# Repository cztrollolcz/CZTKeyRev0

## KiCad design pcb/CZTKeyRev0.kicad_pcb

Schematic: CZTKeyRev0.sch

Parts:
BJ_LED5V1: Barrel_Jack_Switch; BarrelJackP1
D0, D1, D2, D3, D4, D5, D6, D7, D8, D9, D10, D11, D12, D13, D14, D15, D16, D17, D18, D19, D20, D21, D22, D23, D24, D25, D26, D27, D28, D29, D30, D31, D32, D33, D34, D35, D36, D37, D38, D39, D40, D41, D42, D43, D44, D45, D46, D47, D48, D49, D50, D51, D52, D53, D54, D55, D56, D57, D58, D59, D60, D61, D62, D63, D64, D65, D66, D67, D68, D69, D70, D71, D72, D73, D74, D75, D76, D77, D78, D79, D80, D81, D82, D83, D84, D85, D86: D_Small; D_DO-35_SOD27_P5.08mm_Vertical_KathodeUp
DC1, DC2, DC3, DC4, DC5, DC6, DC7, DC8, DC9, DC10, DC11, DC12, DC13, DC14, DC15, DC16, DC17, DC18, DC19, DC20, DC21, DC22, DC23, DC24, DC25, DC26, DC27, DC28, DC29, DC30, DC31, DC32, DC33, DC34, DC35, DC36, DC37, DC38, DC39, DC40, DC41, DC42, DC43, DC44, DC45, DC46, DC47, DC48, DC49, DC50, DC51, DC52, DC53, DC54, DC55, DC56, DC57, DC58, DC59, DC60, DC61, DC62, DC63, DC64, DC65, DC66, DC67, DC68, DC69, DC70, DC71, DC72, DC73, DC74, DC75, DC76, DC78, DC79, DC80, DC81, DC82, DC83, DC84, DC85, DC86, DC87: 100n; C_0805_2012Metric_Pad1.15x1.40mm_HandSolder
ENC1: Rotary_Encoder_Switch; RotaryEncoder_Alps_EC11E-Switch_Vertical_H20mm
EXT_IC1: 74LVC1G17GV,125; SOT95P275X110-5N; Mouser Part Number 771-LVC1G17GV125
LED1, LED2, LED3, LED4, LED5, LED6, LED7, LED8, LED9, LED10, LED11, LED12, LED13, LED14, LED15, LED16, LED17, LED18, LED19, LED20, LED21, LED22, LED23, LED24, LED25, LED26, LED27, LED28, LED29, LED30, LED31, LED32, LED33, LED34, LED35, LED36, LED37, LED38, LED39, LED40, LED41, LED42, LED43, LED44, LED45, LED46, LED47, LED48, LED49, LED50, LED51, LED52, LED53, LED54, LED55, LED56, LED57, LED58, LED59, LED60, LED61, LED62, LED63, LED64, LED65, LED66, LED67, LED68, LED69, LED70, LED71, LED72, LED73, LED74, LED75, LED76, LED78, LED79, LED80, LED81, LED82, LED83, LED84, LED85, LED86, LED87: YS-SK6812MINI-E; SK6812MINIE-simple
MX_0, MX_1, MX_2, MX_3, MX_4, MX_5, MX_6, MX_7, MX_8, MX_9: MX-NoLED; MX-1U-NoLED
MX_A1: MX-NoLED; MX-1U-NoLED
MX_ALT_L1: MX-NoLED; MX-1.25U-NoLED
MX_ALT_R1: MX-NoLED; MX-1.5U-NoLED
MX_B1: MX-NoLED; MX-1U-NoLED
MX_BACKSPACE1: MX-NoLED; MX-2U-NoLED
MX_BCKSLASH1: MX-NoLED; MX-1.5U-NoLED
MX_BR_L1: MX-NoLED; MX-1U-NoLED
MX_BR_R1: MX-NoLED; MX-1U-NoLED
MX_C1: MX-NoLED; MX-1U-NoLED
MX_CAPS1: MX-NoLED; MX-1.75U-NoLED
MX_COMMA1: MX-NoLED; MX-1U-NoLED
MX_CTRL_L1: MX-NoLED; MX-1.25U-NoLED
MX_CTRL_R1: MX-NoLED; MX-1.5U-NoLED
MX_D1: MX-NoLED; MX-1U-NoLED
MX_DELETE1: MX-NoLED; MX-1U-NoLED
MX_DOT1: MX-NoLED; MX-1U-NoLED
MX_DOWN1: MX-NoLED; MX-1U-NoLED
MX_E1: MX-NoLED; MX-1U-NoLED
MX_ENTER1: MX-NoLED; MX-2.25U-NoLED
MX_EQUAL1: MX-NoLED; MX-1U-NoLED
MX_ESC1: MX-NoLED; MX-1U-NoLED
MX_F0, MX_F1, MX_F2, MX_F3, MX_F4, MX_F5, MX_F6, MX_F7, MX_F8, MX_F9, MX_F10, MX_F11, MX_F12: MX-NoLED; MX-1U-NoLED
MX_G1: MX-NoLED; MX-1U-NoLED
MX_H1: MX-NoLED; MX-1U-NoLED
MX_I1: MX-NoLED; MX-1U-NoLED
MX_INSERT1: MX-NoLED; MX-1U-NoLED
MX_J1: MX-NoLED; MX-1U-NoLED
MX_K1: MX-NoLED; MX-1U-NoLED
MX_L1: MX-NoLED; MX-1U-NoLED
MX_LEFT1: MX-NoLED; MX-1U-NoLED
MX_M1: MX-NoLED; MX-1U-NoLED
MX_MAC1, MX_MAC2, MX_MAC3, MX_MAC4, MX_MAC5: MX-NoLED; MX-1U-NoLED
MX_MINUS1: MX-NoLED; MX-1U-NoLED
MX_N1: MX-NoLED; MX-1U-NoLED
MX_O1: MX-NoLED; MX-1U-NoLED
MX_P1: MX-NoLED; MX-1U-NoLED
MX_PGDWN1: MX-NoLED; MX-1U-NoLED
MX_PGUP1: MX-NoLED; MX-1U-NoLED
MX_PRTSC1: MX-NoLED; MX-1U-NoLED
MX_Q1: MX-NoLED; MX-1U-NoLED
MX_QUOTE1: MX-NoLED; MX-1U-NoLED
MX_R1: MX-NoLED; MX-1U-NoLED
MX_RIGHT1: MX-NoLED; MX-1U-NoLED
MX_S1: MX-NoLED; MX-1U-NoLED
MX_SEMIC1: MX-NoLED; MX-1U-NoLED
MX_SHIFT_L1: MX-NoLED; MX-2.25U-NoLED
MX_SHIFT_R1: MX-NoLED; MX-1.75U-NoLED
MX_SLASH1: MX-NoLED; MX-1U-NoLED
MX_SPACE1: MX-NoLED; MX-6.25U-NoLED
MX_T1: MX-NoLED; MX-1U-NoLED
MX_TAB1: MX-NoLED; MX-1.5U-NoLED
MX_TILDE1: MX-NoLED; MX-1U-NoLED
MX_U1: MX-NoLED; MX-1U-NoLED
MX_UP1: MX-NoLED; MX-1U-NoLED
MX_V1: MX-NoLED; MX-1U-NoLED
MX_W1: MX-NoLED; MX-1U-NoLED
MX_WIN1: MX-NoLED; MX-1.25U-NoLED
MX_X1: MX-NoLED; MX-1U-NoLED
MX_Y1: MX-NoLED; MX-1U-NoLED
MX_Z1: MX-NoLED; MX-1U-NoLED
OLED1: SSD1306; 128x64OLED
PCB_BC1: MountingHole_Pad; MountingHole_2.2mm_M2_Pad
PCB_BL1: MountingHole_Pad; MountingHole_2.2mm_M2_Pad
PCB_BR1: MountingHole_Pad; MountingHole_2.2mm_M2_Pad
PCB_MC1: MountingHole_Pad; MountingHole_2.2mm_M2_Pad
PCB_TC1: MountingHole_Pad; MountingHole_2.2mm_M2_Pad
PCB_TL1: MountingHole_Pad; MountingHole_2.2mm_M2_Pad
PCB_TR1: MountingHole_Pad; MountingHole_2.2mm_M2_Pad
PLATE_BC1: MountingHole_Pad; MountingHole_2.2mm_M2_Pad
PLATE_BL1: MountingHole_Pad; MountingHole_2.2mm_M2_Pad
PLATE_BR1: MountingHole_Pad; MountingHole_2.2mm_M2_Pad
PLATE_TC1: MountingHole_Pad; MountingHole_2.2mm_M2_Pad
PLATE_TL1: MountingHole_Pad; MountingHole_2.2mm_M2_Pad
PLATE_TR1: MountingHole_Pad; MountingHole_2.2mm_M2_Pad
R1: 300-500 - C422828; R_0805_2012Metric_Pad1.15x1.40mm_HandSolder
U1: proton_c

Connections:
+5V: OLED1.2 (VCC), U1.5V (VBUS(5V_RAW))
COL0: ENC1.S1, MX_MAC1.1 (COL), MX_MAC2.1 (COL), MX_MAC3.1 (COL), MX_MAC4.1 (COL), MX_MAC5.1 (COL), U1.A2
COL1: MX_CAPS1.1 (COL), MX_CTRL_L1.1 (COL), MX_ESC1.1 (COL), MX_SHIFT_L1.1 (COL), MX_TAB1.1 (COL), MX_TILDE1.1 (COL), U1.A1
COL2: MX_1.1 (COL), MX_A1.1 (COL), MX_F1.1 (COL), MX_Q1.1 (COL), MX_WIN1.1 (COL), MX_Z1.1 (COL), U1.A0
COL3: MX_2.1 (COL), MX_ALT_L1.1 (COL), MX_F2.1 (COL), MX_S1.1 (COL), MX_W1.1 (COL), MX_X1.1 (COL), U1.B8
COL4: MX_3.1 (COL), MX_C1.1 (COL), MX_D1.1 (COL), MX_E1.1 (COL), MX_F3.1 (COL), U1.B13 (PB13/SCLK)
COL5: MX_4.1 (COL), MX_F0.1 (COL), MX_F4.1 (COL), MX_R1.1 (COL), MX_V1.1 (COL), U1.B14 (PB14/MISO)
COL6: MX_5.1 (COL), MX_B1.1 (COL), MX_F5.1 (COL), MX_G1.1 (COL), MX_SPACE1.1 (COL), MX_T1.1 (COL), U1.B15 (PB15/MOSI)
COL7: MX_6.1 (COL), MX_F6.1 (COL), MX_H1.1 (COL), MX_N1.1 (COL), MX_Y1.1 (COL), U1.B9
COL8: MX_7.1 (COL), MX_F7.1 (COL), MX_J1.1 (COL), MX_M1.1 (COL), MX_U1.1 (COL), U1.A4 (PA4/SPEAKER1)
COL9: MX_8.1 (COL), MX_COMMA1.1 (COL), MX_F8.1 (COL), MX_I1.1 (COL), MX_K1.1 (COL), U1.A5 (PA5/SPEAKER2)
COL10: MX_9.1 (COL), MX_ALT_R1.1 (COL), MX_DOT1.1 (COL), MX_F9.1 (COL), MX_L1.1 (COL), MX_O1.1 (COL), U1.A6
COL11: MX_0.1 (COL), MX_CTRL_R1.1 (COL), MX_F10.1 (COL), MX_P1.1 (COL), MX_SEMIC1.1 (COL), MX_SLASH1.1 (COL), U1.A7
COL12: MX_BR_R1.1 (COL), MX_F11.1 (COL), MX_LEFT1.1 (COL), MX_MINUS1.1 (COL), MX_QUOTE1.1 (COL), MX_SHIFT_R1.1 (COL), U1.A8
COL13: MX_BR_L1.1 (COL), MX_DOWN1.1 (COL), MX_ENTER1.1 (COL), MX_EQUAL1.1 (COL), MX_F12.1 (COL), U1.A15
COL14: MX_BACKSPACE1.1 (COL), MX_BCKSLASH1.1 (COL), MX_PRTSC1.1 (COL), MX_UP1.1 (COL), U1.A14 (PA14/SWCLK)
COL15: MX_DELETE1.1 (COL), MX_INSERT1.1 (COL), MX_PGDWN1.1 (COL), MX_PGUP1.1 (COL), MX_RIGHT1.1 (COL), U1.A13 (PA13/SWDIO)
ENC_A: ENC1.A, U1.B11
ENC_B: ENC1.B, U1.B12
ENC_S2: D0.2 (A), ENC1.S2
EXT_5V: BJ_LED5V1.1, DC1.2, DC2.2, DC3.2, DC4.2, DC5.2, DC6.2, DC7.2, DC8.2, DC9.2, DC10.2, DC11.2, DC12.2, DC13.2, DC14.2, DC15.2, DC16.2, DC17.2, DC18.2, DC19.2, DC20.2, DC21.2, DC22.2, DC23.2, DC24.2, DC25.2, DC26.2, DC27.2, DC28.2, DC29.2, DC30.2, DC31.2, DC32.2, DC33.2, DC34.2, DC35.2, DC36.2, DC37.2, DC38.2, DC39.2, DC40.2, DC41.2, DC42.2, DC43.2, DC44.2, DC45.2, DC46.2, DC47.2, DC48.2, DC49.2, DC50.2, DC51.2, DC52.2, DC53.2, DC54.2, DC55.2, DC56.2, DC57.2, DC58.2, DC59.2, DC60.2, DC61.1, DC62.2, DC63.2, DC64.2, DC65.2, DC66.2, DC67.2, DC68.2, DC69.2, DC70.2, DC71.2, DC72.2, DC73.2, DC74.2, DC75.2, DC76.1, DC78.1, DC79.1, DC80.1, DC81.1, DC82.1, DC83.1, DC84.1, DC85.1, DC86.1, DC87.1, EXT_IC1.5 (VCC), LED1.1 (VDD), LED2.1 (VDD), LED3.1 (VDD), LED4.1 (VDD), LED5.1 (VDD), LED6.1 (VDD), LED7.1 (VDD), LED8.1 (VDD), LED9.1 (VDD), LED10.1 (VDD), LED11.1 (VDD), LED12.1 (VDD), LED13.1 (VDD), LED14.1 (VDD), LED15.1 (VDD), LED16.1 (VDD), LED17.1 (VDD), LED18.1 (VDD), LED19.1 (VDD), LED20.1 (VDD), LED21.1 (VDD), LED22.1 (VDD), LED23.1 (VDD), LED24.1 (VDD), LED25.1 (VDD), LED26.1 (VDD), LED27.1 (VDD), LED28.1 (VDD), LED29.1 (VDD), LED30.1 (VDD), LED31.1 (VDD), LED32.1 (VDD), LED33.1 (VDD), LED34.1 (VDD), LED35.1 (VDD), LED36.1 (VDD), LED37.1 (VDD), LED38.1 (VDD), LED39.1 (VDD), LED40.1 (VDD), LED41.1 (VDD), LED42.1 (VDD), LED43.1 (VDD), LED44.1 (VDD), LED45.1 (VDD), LED46.1 (VDD), LED47.1 (VDD), LED48.1 (VDD), LED49.1 (VDD), LED50.1 (VDD), LED51.1 (VDD), LED52.1 (VDD), LED53.1 (VDD), LED54.1 (VDD), LED55.1 (VDD), LED56.1 (VDD), LED57.1 (VDD), LED58.1 (VDD), LED59.1 (VDD), LED60.1 (VDD), LED61.1 (VDD), LED62.1 (VDD), LED63.1 (VDD), LED64.1 (VDD), LED65.1 (VDD), LED66.1 (VDD), LED67.1 (VDD), LED68.1 (VDD), LED69.1 (VDD), LED70.1 (VDD), LED71.1 (VDD), LED72.1 (VDD), LED73.1 (VDD), LED74.1 (VDD), LED75.1 (VDD), LED76.1 (VDD), LED78.1 (VDD), LED79.1 (VDD), LED80.1 (VDD), LED81.1 (VDD), LED82.1 (VDD), LED83.1 (VDD), LED84.1 (VDD), LED85.1 (VDD), LED86.1 (VDD), LED87.1 (VDD)
EXT_GND: BJ_LED5V1.2, DC1.1, DC2.1, DC3.1, DC4.1, DC5.1, DC6.1, DC7.1, DC8.1, DC9.1, DC10.1, DC11.1, DC12.1, DC13.1, DC14.1, DC15.1, DC16.1, DC17.1, DC18.1, DC19.1, DC20.1, DC21.1, DC22.1, DC23.1, DC24.1, DC25.1, DC26.1, DC27.1, DC28.1, DC29.1, DC30.1, DC31.1, DC32.1, DC33.1, DC34.1, DC35.1, DC36.1, DC37.1, DC38.1, DC39.1, DC40.1, DC41.1, DC42.1, DC43.1, DC44.1, DC45.1, DC46.1, DC47.1, DC48.1, DC49.1, DC50.1, DC51.1, DC52.1, DC53.1, DC54.1, DC55.1, DC56.1, DC57.1, DC58.1, DC59.1, DC60.1, DC61.2, DC62.1, DC63.1, DC64.1, DC65.1, DC66.1, DC67.1, DC68.1, DC69.1, DC70.1, DC71.1, DC72.1, DC73.1, DC74.1, DC75.1, DC76.2, DC78.2, DC79.2, DC80.2, DC81.2, DC82.2, DC83.2, DC84.2, DC85.2, DC86.2, DC87.2, ENC1.C, EXT_IC1.3 (GND), LED1.3 (VSS), LED2.3 (VSS), LED3.3 (VSS), LED4.3 (VSS), LED5.3 (VSS), LED6.3 (VSS), LED7.3 (VSS), LED8.3 (VSS), LED9.3 (VSS), LED10.3 (VSS), LED11.3 (VSS), LED12.3 (VSS), LED13.3 (VSS), LED14.3 (VSS), LED15.3 (VSS), LED16.3 (VSS), LED17.3 (VSS), LED18.3 (VSS), LED19.3 (VSS), LED20.3 (VSS), LED21.3 (VSS), LED22.3 (VSS), LED23.3 (VSS), LED24.3 (VSS), LED25.3 (VSS), LED26.3 (VSS), LED27.3 (VSS), LED28.3 (VSS), LED29.3 (VSS), LED30.3 (VSS), LED31.3 (VSS), LED32.3 (VSS), LED33.3 (VSS), LED34.3 (VSS), LED35.3 (VSS), LED36.3 (VSS), LED37.3 (VSS), LED38.3 (VSS), LED39.3 (VSS), LED40.3 (VSS), LED41.3 (VSS), LED42.3 (VSS), LED43.3 (VSS), LED44.3 (VSS), LED45.3 (VSS), LED46.3 (VSS), LED47.3 (VSS), LED48.3 (VSS), LED49.3 (VSS), LED50.3 (VSS), LED51.3 (VSS), LED52.3 (VSS), LED53.3 (VSS), LED54.3 (VSS), LED55.3 (VSS), LED56.3 (VSS), LED57.3 (VSS), LED58.3 (VSS), LED59.3 (VSS), LED60.3 (VSS), LED61.3 (VSS), LED62.3 (VSS), LED63.3 (VSS), LED64.3 (VSS), LED65.3 (VSS), LED66.3 (VSS), LED67.3 (VSS), LED68.3 (VSS), LED69.3 (VSS), LED70.3 (VSS), LED71.3 (VSS), LED72.3 (VSS), LED73.3 (VSS), LED74.3 (VSS), LED75.3 (VSS), LED76.3 (VSS), LED78.3 (VSS), LED79.3 (VSS), LED80.3 (VSS), LED81.3 (VSS), LED82.3 (VSS), LED83.3 (VSS), LED84.3 (VSS), LED85.3 (VSS), LED86.3 (VSS), LED87.3 (VSS), OLED1.1 (GND), U1.GND
unnamed: D1.2 (A), MX_ESC1.2 (ROW)
unnamed: D2.2 (A), MX_F1.2 (ROW)
unnamed: D3.2 (A), MX_F2.2 (ROW)
unnamed: D4.2 (A), MX_F3.2 (ROW)
unnamed: D5.2 (A), MX_F4.2 (ROW)
unnamed: D6.2 (A), MX_F5.2 (ROW)
unnamed: D7.2 (A), MX_F6.2 (ROW)
unnamed: D8.2 (A), MX_F7.2 (ROW)
unnamed: D9.2 (A), MX_F8.2 (ROW)
unnamed: D10.2 (A), MX_F9.2 (ROW)
unnamed: D11.2 (A), MX_F10.2 (ROW)
unnamed: D12.2 (A), MX_F11.2 (ROW)
unnamed: D13.2 (A), MX_F12.2 (ROW)
unnamed: D14.2 (A), MX_PRTSC1.2 (ROW)
unnamed: D15.2 (A), MX_TILDE1.2 (ROW)
unnamed: D16.2 (A), MX_1.2 (ROW)
unnamed: D17.2 (A), MX_2.2 (ROW)
unnamed: D18.2 (A), MX_3.2 (ROW)
unnamed: D19.2 (A), MX_4.2 (ROW)
unnamed: D20.2 (A), MX_5.2 (ROW)
unnamed: D21.2 (A), MX_6.2 (ROW)
unnamed: D22.2 (A), MX_7.2 (ROW)
unnamed: D23.2 (A), MX_8.2 (ROW)
unnamed: D24.2 (A), MX_9.2 (ROW)
unnamed: D25.2 (A), MX_0.2 (ROW)
unnamed: D26.2 (A), MX_MINUS1.2 (ROW)
unnamed: D27.2 (A), MX_EQUAL1.2 (ROW)
unnamed: D28.2 (A), MX_BACKSPACE1.2 (ROW)
unnamed: D29.2 (A), MX_INSERT1.2 (ROW)
unnamed: D30.2 (A), MX_TAB1.2 (ROW)
unnamed: D31.2 (A), MX_Q1.2 (ROW)
unnamed: D32.2 (A), MX_W1.2 (ROW)
unnamed: D33.2 (A), MX_E1.2 (ROW)
unnamed: D34.2 (A), MX_R1.2 (ROW)
unnamed: D35.2 (A), MX_T1.2 (ROW)
unnamed: D36.2 (A), MX_Y1.2 (ROW)
unnamed: D37.2 (A), MX_U1.2 (ROW)
unnamed: D38.2 (A), MX_I1.2 (ROW)
unnamed: D39.2 (A), MX_O1.2 (ROW)
unnamed: D40.2 (A), MX_P1.2 (ROW)
unnamed: D41.2 (A), MX_BR_R1.2 (ROW)
unnamed: D42.2 (A), MX_BR_L1.2 (ROW)
unnamed: D43.2 (A), MX_BCKSLASH1.2 (ROW)
unnamed: D44.2 (A), MX_DELETE1.2 (ROW)
unnamed: D45.2 (A), MX_CAPS1.2 (ROW)
unnamed: D46.2 (A), MX_A1.2 (ROW)
unnamed: D47.2 (A), MX_S1.2 (ROW)
unnamed: D48.2 (A), MX_D1.2 (ROW)
unnamed: D49.2 (A), MX_F0.2 (ROW)
unnamed: D50.2 (A), MX_G1.2 (ROW)
unnamed: D51.2 (A), MX_H1.2 (ROW)
unnamed: D52.2 (A), MX_J1.2 (ROW)
unnamed: D53.2 (A), MX_K1.2 (ROW)
unnamed: D54.2 (A), MX_L1.2 (ROW)
unnamed: D55.2 (A), MX_SEMIC1.2 (ROW)
unnamed: D56.2 (A), MX_QUOTE1.2 (ROW)
unnamed: D57.2 (A), MX_ENTER1.2 (ROW)
unnamed: D58.2 (A), MX_PGUP1.2 (ROW)
unnamed: D59.2 (A), MX_SHIFT_L1.2 (ROW)
unnamed: D60.2 (A), MX_Z1.2 (ROW)
unnamed: D61.2 (A), MX_X1.2 (ROW)
unnamed: D62.2 (A), MX_C1.2 (ROW)
unnamed: D63.2 (A), MX_V1.2 (ROW)
unnamed: D64.2 (A), MX_B1.2 (ROW)
unnamed: D65.2 (A), MX_N1.2 (ROW)
unnamed: D66.2 (A), MX_M1.2 (ROW)
unnamed: D67.2 (A), MX_COMMA1.2 (ROW)
unnamed: D68.2 (A), MX_DOT1.2 (ROW)
unnamed: D69.2 (A), MX_SLASH1.2 (ROW)
unnamed: D70.2 (A), MX_SHIFT_R1.2 (ROW)
unnamed: D71.2 (A), MX_UP1.2 (ROW)
unnamed: D72.2 (A), MX_PGDWN1.2 (ROW)
unnamed: D73.2 (A), MX_CTRL_L1.2 (ROW)
unnamed: D74.2 (A), MX_WIN1.2 (ROW)
unnamed: D75.2 (A), MX_ALT_L1.2 (ROW)
unnamed: D76.2 (A), MX_SPACE1.2 (ROW)
unnamed: D77.2 (A), MX_ALT_R1.2 (ROW)
unnamed: D78.2 (A), MX_CTRL_R1.2 (ROW)
unnamed: D79.2 (A), MX_LEFT1.2 (ROW)
unnamed: D80.2 (A), MX_DOWN1.2 (ROW)
unnamed: D81.2 (A), MX_RIGHT1.2 (ROW)
unnamed: D82.2 (A), MX_MAC1.2 (ROW)
unnamed: D83.2 (A), MX_MAC2.2 (ROW)
unnamed: D84.2 (A), MX_MAC3.2 (ROW)
unnamed: D85.2 (A), MX_MAC4.2 (ROW)
unnamed: D86.2 (A), MX_MAC5.2 (ROW)
unnamed: EXT_IC1.4 (Y), LED1.4 (DIN)
unnamed: LED1.2 (DOUT), LED2.4 (DIN)
unnamed: LED2.2 (DOUT), LED3.4 (DIN)
unnamed: LED3.2 (DOUT), LED4.4 (DIN)
unnamed: LED4.2 (DOUT), LED5.4 (DIN)
unnamed: LED5.2 (DOUT), LED6.4 (DIN)
unnamed: LED6.2 (DOUT), LED7.4 (DIN)
unnamed: LED7.2 (DOUT), LED8.4 (DIN)
unnamed: LED8.2 (DOUT), LED9.4 (DIN)
unnamed: LED10.2 (DOUT), LED11.4 (DIN)
unnamed: LED9.2 (DOUT), LED10.4 (DIN)
unnamed: LED11.2 (DOUT), LED12.4 (DIN)
unnamed: LED12.2 (DOUT), LED13.4 (DIN)
unnamed: LED13.2 (DOUT), LED14.4 (DIN)
unnamed: LED14.2 (DOUT), LED30.4 (DIN)
unnamed: LED15.2 (DOUT), LED31.4 (DIN)
unnamed: LED15.4 (DIN), LED16.2 (DOUT)
unnamed: LED16.4 (DIN), LED17.2 (DOUT)
unnamed: LED17.4 (DIN), LED18.2 (DOUT)
unnamed: LED18.4 (DIN), LED19.2 (DOUT)
unnamed: LED19.4 (DIN), LED20.2 (DOUT)
unnamed: LED20.4 (DIN), LED21.2 (DOUT)
unnamed: LED21.4 (DIN), LED22.2 (DOUT)
unnamed: LED22.4 (DIN), LED23.2 (DOUT)
unnamed: LED23.4 (DIN), LED24.2 (DOUT)
unnamed: LED24.4 (DIN), LED25.2 (DOUT)
unnamed: LED25.4 (DIN), LED26.2 (DOUT)
unnamed: LED26.4 (DIN), LED27.2 (DOUT)
unnamed: LED27.4 (DIN), LED28.2 (DOUT)
unnamed: LED28.4 (DIN), LED29.2 (DOUT)
unnamed: LED29.4 (DIN), LED30.2 (DOUT)
unnamed: LED31.2 (DOUT), LED32.4 (DIN)
unnamed: LED32.2 (DOUT), LED33.4 (DIN)
unnamed: LED33.2 (DOUT), LED34.4 (DIN)
unnamed: LED34.2 (DOUT), LED35.4 (DIN)
unnamed: LED35.2 (DOUT), LED36.4 (DIN)
unnamed: LED36.2 (DOUT), LED37.4 (DIN)
unnamed: LED37.2 (DOUT), LED38.4 (DIN)
unnamed: LED38.2 (DOUT), LED39.4 (DIN)
unnamed: LED39.2 (DOUT), LED40.4 (DIN)
unnamed: LED40.2 (DOUT), LED41.4 (DIN)
unnamed: LED41.2 (DOUT), LED42.4 (DIN)
unnamed: LED42.2 (DOUT), LED43.4 (DIN)
unnamed: LED43.2 (DOUT), LED44.4 (DIN)
unnamed: LED44.2 (DOUT), LED45.4 (DIN)
unnamed: LED45.2 (DOUT), LED46.4 (DIN)
unnamed: LED46.2 (DOUT), LED61.4 (DIN)
unnamed: LED47.2 (DOUT), LED62.4 (DIN)
unnamed: LED47.4 (DIN), LED48.2 (DOUT)
unnamed: LED48.4 (DIN), LED49.2 (DOUT)
unnamed: LED49.4 (DIN), LED50.2 (DOUT)
unnamed: LED50.4 (DIN), LED51.2 (DOUT)
unnamed: LED51.4 (DIN), LED52.2 (DOUT)
unnamed: LED52.4 (DIN), LED53.2 (DOUT)
unnamed: LED53.4 (DIN), LED54.2 (DOUT)
unnamed: LED54.4 (DIN), LED55.2 (DOUT)
unnamed: LED55.4 (DIN), LED56.2 (DOUT)
unnamed: LED56.4 (DIN), LED57.2 (DOUT)
unnamed: LED57.4 (DIN), LED58.2 (DOUT)
unnamed: LED58.4 (DIN), LED59.2 (DOUT)
unnamed: LED59.4 (DIN), LED60.2 (DOUT)
unnamed: LED60.4 (DIN), LED61.2 (DOUT)
unnamed: LED62.2 (DOUT), LED63.4 (DIN)
unnamed: LED63.2 (DOUT), LED64.4 (DIN)
unnamed: LED64.2 (DOUT), LED65.4 (DIN)
unnamed: LED65.2 (DOUT), LED66.4 (DIN)
unnamed: LED66.2 (DOUT), LED67.4 (DIN)
unnamed: LED67.2 (DOUT), LED68.4 (DIN)
unnamed: LED68.2 (DOUT), LED69.4 (DIN)
unnamed: LED69.2 (DOUT), LED70.4 (DIN)
unnamed: LED70.2 (DOUT), LED71.4 (DIN)
unnamed: LED71.2 (DOUT), LED72.4 (DIN)
unnamed: LED72.2 (DOUT), LED73.4 (DIN)
unnamed: LED73.2 (DOUT), LED74.4 (DIN)
unnamed: LED74.2 (DOUT), LED75.4 (DIN)
unnamed: LED75.2 (DOUT), LED76.4 (DIN)
unnamed: LED76.2 (DOUT), LED87.4 (DIN)
unnamed: LED78.4 (DIN), LED79.2 (DOUT)
unnamed: LED79.4 (DIN), LED80.2 (DOUT)
unnamed: LED80.4 (DIN), LED81.2 (DOUT)
unnamed: LED81.4 (DIN), LED82.2 (DOUT)
unnamed: LED82.4 (DIN), LED83.2 (DOUT)
unnamed: LED83.4 (DIN), LED84.2 (DOUT)
unnamed: LED84.4 (DIN), LED85.2 (DOUT)
unnamed: LED85.4 (DIN), LED86.2 (DOUT)
unnamed: LED86.4 (DIN), LED87.2 (DOUT)
unnamed: R1.2, U1.B10
OLEDSCL: OLED1.3 (SCL), U1.B6 (PB6/SCL)
OLEDSDA: OLED1.4 (SDA), U1.B7 (PB7/SDA)
RGB_MATRIX: EXT_IC1.2 (A), R1.1
ROW0: D0.1 (K), D1.1 (K), D2.1 (K), D3.1 (K), D4.1 (K), D5.1 (K), D6.1 (K), D7.1 (K), D8.1 (K), D9.1 (K), D10.1 (K), D11.1 (K), D12.1 (K), D13.1 (K), D14.1 (K), U1.B0
ROW1: D15.1 (K), D16.1 (K), D17.1 (K), D18.1 (K), D19.1 (K), D20.1 (K), D21.1 (K), D22.1 (K), D23.1 (K), D24.1 (K), D25.1 (K), D26.1 (K), D27.1 (K), D28.1 (K), D29.1 (K), D82.1 (K), U1.B1
ROW2: D30.1 (K), D31.1 (K), D32.1 (K), D33.1 (K), D34.1 (K), D35.1 (K), D36.1 (K), D37.1 (K), D38.1 (K), D39.1 (K), D40.1 (K), D41.1 (K), D42.1 (K), D43.1 (K), D44.1 (K), D83.1 (K), U1.B2
ROW3: D45.1 (K), D46.1 (K), D47.1 (K), D48.1 (K), D49.1 (K), D50.1 (K), D51.1 (K), D52.1 (K), D53.1 (K), D54.1 (K), D55.1 (K), D56.1 (K), D57.1 (K), D58.1 (K), D84.1 (K), U1.B3
ROW4: D59.1 (K), D60.1 (K), D61.1 (K), D62.1 (K), D63.1 (K), D64.1 (K), D65.1 (K), D66.1 (K), D67.1 (K), D68.1 (K), D69.1 (K), D70.1 (K), D71.1 (K), D72.1 (K), D85.1 (K), U1.B4
ROW5: D73.1 (K), D74.1 (K), D75.1 (K), D76.1 (K), D77.1 (K), D78.1 (K), D79.1 (K), D80.1 (K), D81.1 (K), D86.1 (K), U1.B5
VCC: U1.3.3V (VCC/3.3v)

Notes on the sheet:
MCU
EXTERNAL POWER SUPPLY
MOUNTING HOLES
OLED
ROTARY ENCODER
SWITCH MATRIX
SK6812MINI-E MATRIX includes the 74LVC1G17GV,125
DecouplingCapacitors - C49678 (0805)

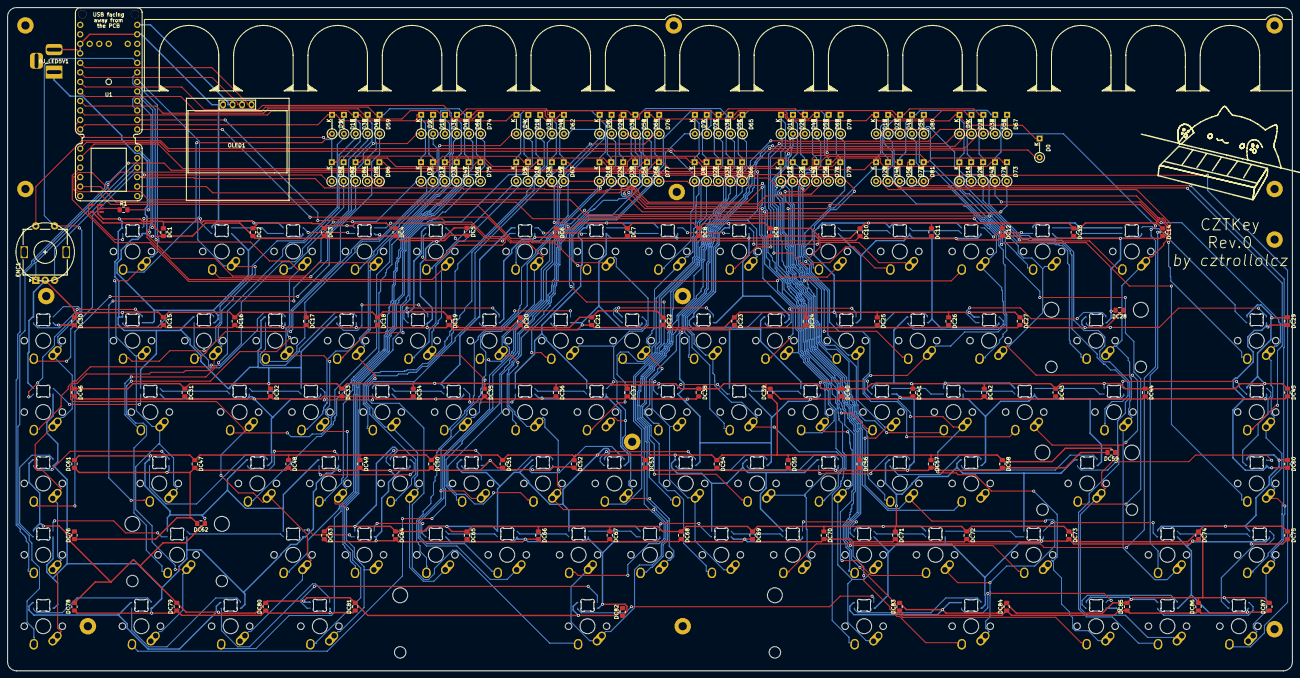
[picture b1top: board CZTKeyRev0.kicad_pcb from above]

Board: 2 copper layers, 342.9 x 177.0 mm, 364 parts (0 on the bottom side), 204 nets.

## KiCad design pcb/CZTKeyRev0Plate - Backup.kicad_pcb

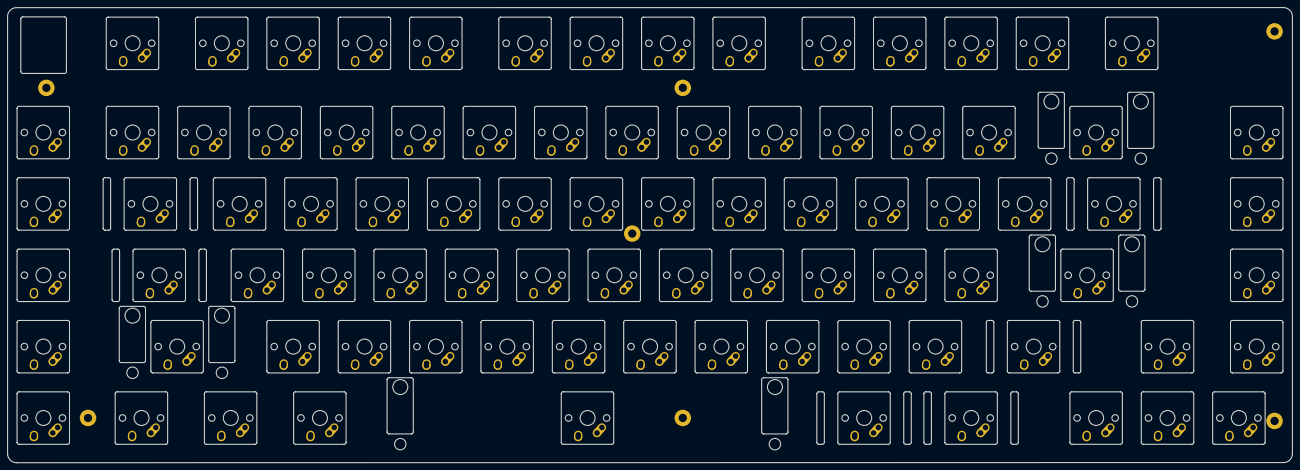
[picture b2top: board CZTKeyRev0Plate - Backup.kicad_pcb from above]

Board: 2 copper layers, 342.9 x 121.5 mm, 93 parts (0 on the bottom side), 16 nets, no tracks yet.

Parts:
MX_0, MX_1, MX_2, MX_3, MX_4, MX_5, MX_6, MX_7, MX_8, MX_9: MX-NoLED; MX-1U-NoLED
MX_A1: MX-NoLED; MX-1U-NoLED
MX_ALT_L1: MX-NoLED; MX-1.25U-NoLED
MX_ALT_R1: MX-NoLED; MX-1.5U-NoLED
MX_B1: MX-NoLED; MX-1U-NoLED
MX_BACKSPACE1: MX-NoLED; MX-2U-NoLED
MX_BCKSLASH1: MX-NoLED; MX-1.5U-NoLED
MX_BR_L1: MX-NoLED; MX-1U-NoLED
MX_BR_R1: MX-NoLED; MX-1U-NoLED
MX_C1: MX-NoLED; MX-1U-NoLED
MX_CAPS1: MX-NoLED; MX-1.75U-NoLED
MX_COMMA1: MX-NoLED; MX-1U-NoLED
MX_CTRL_L1: MX-NoLED; MX-1.25U-NoLED
MX_CTRL_R1: MX-NoLED; MX-1.5U-NoLED
MX_D1: MX-NoLED; MX-1U-NoLED
MX_DELETE1: MX-NoLED; MX-1U-NoLED
MX_DOT1: MX-NoLED; MX-1U-NoLED
MX_DOWN1: MX-NoLED; MX-1U-NoLED
MX_E1: MX-NoLED; MX-1U-NoLED
MX_ENTER1: MX-NoLED; MX-2.25U-NoLED
MX_EQUAL1: MX-NoLED; MX-1U-NoLED
MX_ESC1: MX-NoLED; MX-1U-NoLED
MX_F0, MX_F1, MX_F2, MX_F3, MX_F4, MX_F5, MX_F6, MX_F7, MX_F8, MX_F9, MX_F10, MX_F11, MX_F12: MX-NoLED; MX-1U-NoLED
MX_G1: MX-NoLED; MX-1U-NoLED
MX_H1: MX-NoLED; MX-1U-NoLED
MX_I1: MX-NoLED; MX-1U-NoLED
MX_INSERT1: MX-NoLED; MX-1U-NoLED
MX_J1: MX-NoLED; MX-1U-NoLED
MX_K1: MX-NoLED; MX-1U-NoLED
MX_L1: MX-NoLED; MX-1U-NoLED
MX_LEFT1: MX-NoLED; MX-1U-NoLED
MX_M1: MX-NoLED; MX-1U-NoLED
MX_MAC1, MX_MAC2, MX_MAC3, MX_MAC4, MX_MAC5: MX-NoLED; MX-1U-NoLED
MX_MINUS1: MX-NoLED; MX-1U-NoLED
MX_N1: MX-NoLED; MX-1U-NoLED
MX_O1: MX-NoLED; MX-1U-NoLED
MX_P1: MX-NoLED; MX-1U-NoLED
MX_PGDWN1: MX-NoLED; MX-1U-NoLED
MX_PGUP1: MX-NoLED; MX-1U-NoLED
MX_PRTSC1: MX-NoLED; MX-1U-NoLED
MX_Q1: MX-NoLED; MX-1U-NoLED
MX_QUOTE1: MX-NoLED; MX-1U-NoLED
MX_R1: MX-NoLED; MX-1U-NoLED
MX_RIGHT1: MX-NoLED; MX-1U-NoLED
MX_S1: MX-NoLED; MX-1U-NoLED
MX_SEMIC1: MX-NoLED; MX-1U-NoLED
MX_SHIFT_L1: MX-NoLED; MX-2.25U-NoLED
MX_SHIFT_R1: MX-NoLED; MX-1.75U-NoLED
MX_SLASH1: MX-NoLED; MX-1U-NoLED
MX_SPACE1: MX-NoLED; MX-6.25U-NoLED
MX_T1: MX-NoLED; MX-1U-NoLED
MX_TAB1: MX-NoLED; MX-1.5U-NoLED
MX_TILDE1: MX-NoLED; MX-1U-NoLED
MX_U1: MX-NoLED; MX-1U-NoLED
MX_UP1: MX-NoLED; MX-1U-NoLED
MX_V1: MX-NoLED; MX-1U-NoLED
MX_W1: MX-NoLED; MX-1U-NoLED
MX_WIN1: MX-NoLED; MX-1.25U-NoLED
MX_X1: MX-NoLED; MX-1U-NoLED
MX_Y1: MX-NoLED; MX-1U-NoLED
MX_Z1: MX-NoLED; MX-1U-NoLED
PCB_BC1: MountingHole_Pad; MountingHole_2.2mm_M2_Pad
PCB_BL1: MountingHole_Pad; MountingHole_2.2mm_M2_Pad
PCB_BR1: MountingHole_Pad; MountingHole_2.2mm_M2_Pad
PCB_MC1: MountingHole_Pad; MountingHole_2.2mm_M2_Pad
PCB_TC1: MountingHole_Pad; MountingHole_2.2mm_M2_Pad
PCB_TL1: MountingHole_Pad; MountingHole_2.2mm_M2_Pad
PCB_TR1: MountingHole_Pad; MountingHole_2.2mm_M2_Pad

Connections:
COL0: MX_MAC1.1, MX_MAC2.1, MX_MAC3.1, MX_MAC4.1, MX_MAC5.1
COL1: MX_CAPS1.1, MX_CTRL_L1.1, MX_ESC1.1, MX_SHIFT_L1.1, MX_TAB1.1, MX_TILDE1.1
COL2: MX_1.1, MX_A1.1, MX_F1.1, MX_Q1.1, MX_WIN1.1, MX_Z1.1
COL3: MX_2.1, MX_ALT_L1.1, MX_F2.1, MX_S1.1, MX_W1.1, MX_X1.1
COL4: MX_3.1, MX_C1.1, MX_D1.1, MX_E1.1, MX_F3.1
COL5: MX_4.1, MX_F0.1, MX_F4.1, MX_R1.1, MX_V1.1
COL6: MX_5.1, MX_B1.1, MX_F5.1, MX_G1.1, MX_SPACE1.1, MX_T1.1
COL7: MX_6.1, MX_F6.1, MX_H1.1, MX_N1.1, MX_Y1.1
COL8: MX_7.1, MX_F7.1, MX_J1.1, MX_M1.1, MX_U1.1
COL9: MX_8.1, MX_COMMA1.1, MX_F8.1, MX_I1.1, MX_K1.1
COL10: MX_9.1, MX_ALT_R1.1, MX_DOT1.1, MX_F9.1, MX_L1.1, MX_O1.1
COL11: MX_0.1, MX_CTRL_R1.1, MX_F10.1, MX_P1.1, MX_SEMIC1.1, MX_SLASH1.1
COL12: MX_BR_R1.1, MX_F11.1, MX_LEFT1.1, MX_MINUS1.1, MX_QUOTE1.1, MX_SHIFT_R1.1
COL13: MX_BR_L1.1, MX_DOWN1.1, MX_ENTER1.1, MX_EQUAL1.1, MX_F12.1
COL14: MX_BACKSPACE1.1, MX_BCKSLASH1.1, MX_PRTSC1.1, MX_UP1.1
COL15: MX_DELETE1.1, MX_INSERT1.1, MX_PGDWN1.1, MX_PGUP1.1, MX_RIGHT1.1

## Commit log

2020-11-26 Create LICENSE
2020-11-26 Created dummy files
2020-11-26 submodules
2020-11-26 Proton C libraries for KiCad
2020-11-26 Added layout
2020-11-26 more submodules
2020-11-26 Layout done in PCB, idk done sum stuff
2020-11-28 Edits to layout and sutff
2020-11-28 WS2812B Matrix
2020-11-28 Wired up matrix and renamed WS2812B from D? to WS?
2020-11-28 Positioned things
2020-11-28 Removed 1.25U spacer
2020-11-28 Maybe final?
2020-11-28 did some stuff
2020-11-28 Generated gerber, added silkscreen and more
2020-11-29 Created a BOM and zip of pcb folder
2020-11-29 Added a weird file to .gitignore
2020-11-29 Renamed BOM
2020-11-30 batchcommit
2020-11-30 rgb led submodule
2020-11-30 added mounting pads
2020-11-30 wrong footprint
2020-12-01 sync
2020-12-01 Added the IC for ext 5v and led data
2020-12-03 Organizing lib, gerber and schematic pdf files into subfolders
    Its for easier navigation
2020-12-03 Resistor between MCU and DIN of SK6812MINI-E
2020-12-03 Added footprint to the resistor
    0805 Hand Solder. Altough this is going to be using SMT assembly from jlcpcb I wanted to add an option to see what would happen if it was a 0ohm resistor istead....
2020-12-06 Hopefully final touches
2020-12-06 Wrong format for packaged gerbers
2020-12-09 Im not even sure what I changed, but seems like a lot lol
2020-12-10 FR4 Plate and stuff
2020-12-10 Backup file for Plate PCB
2020-12-10 Plate Gerbers
2020-12-10 New PCB Gerbers
    Needed new gerbers since I made the board slightly bigger
2020-12-10 Zipped the Plate Gerbers
2020-12-10 Create TODO.txt
    TODO: Make the board smaller on the bottom. since I flipped the stabs
2020-12-10 Error in silkscreen
2020-12-10 Possibly better solution to EXT5V
2020-12-11 Footprint of MX_1U key with the LED in it
2020-12-11 Created a PCB which doesnt have flipped keys (aka the correct version)
2020-12-13 Update fp-info-cache
